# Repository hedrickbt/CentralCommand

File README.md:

# CentralCommand
Contextual Electronics CentralCommand project

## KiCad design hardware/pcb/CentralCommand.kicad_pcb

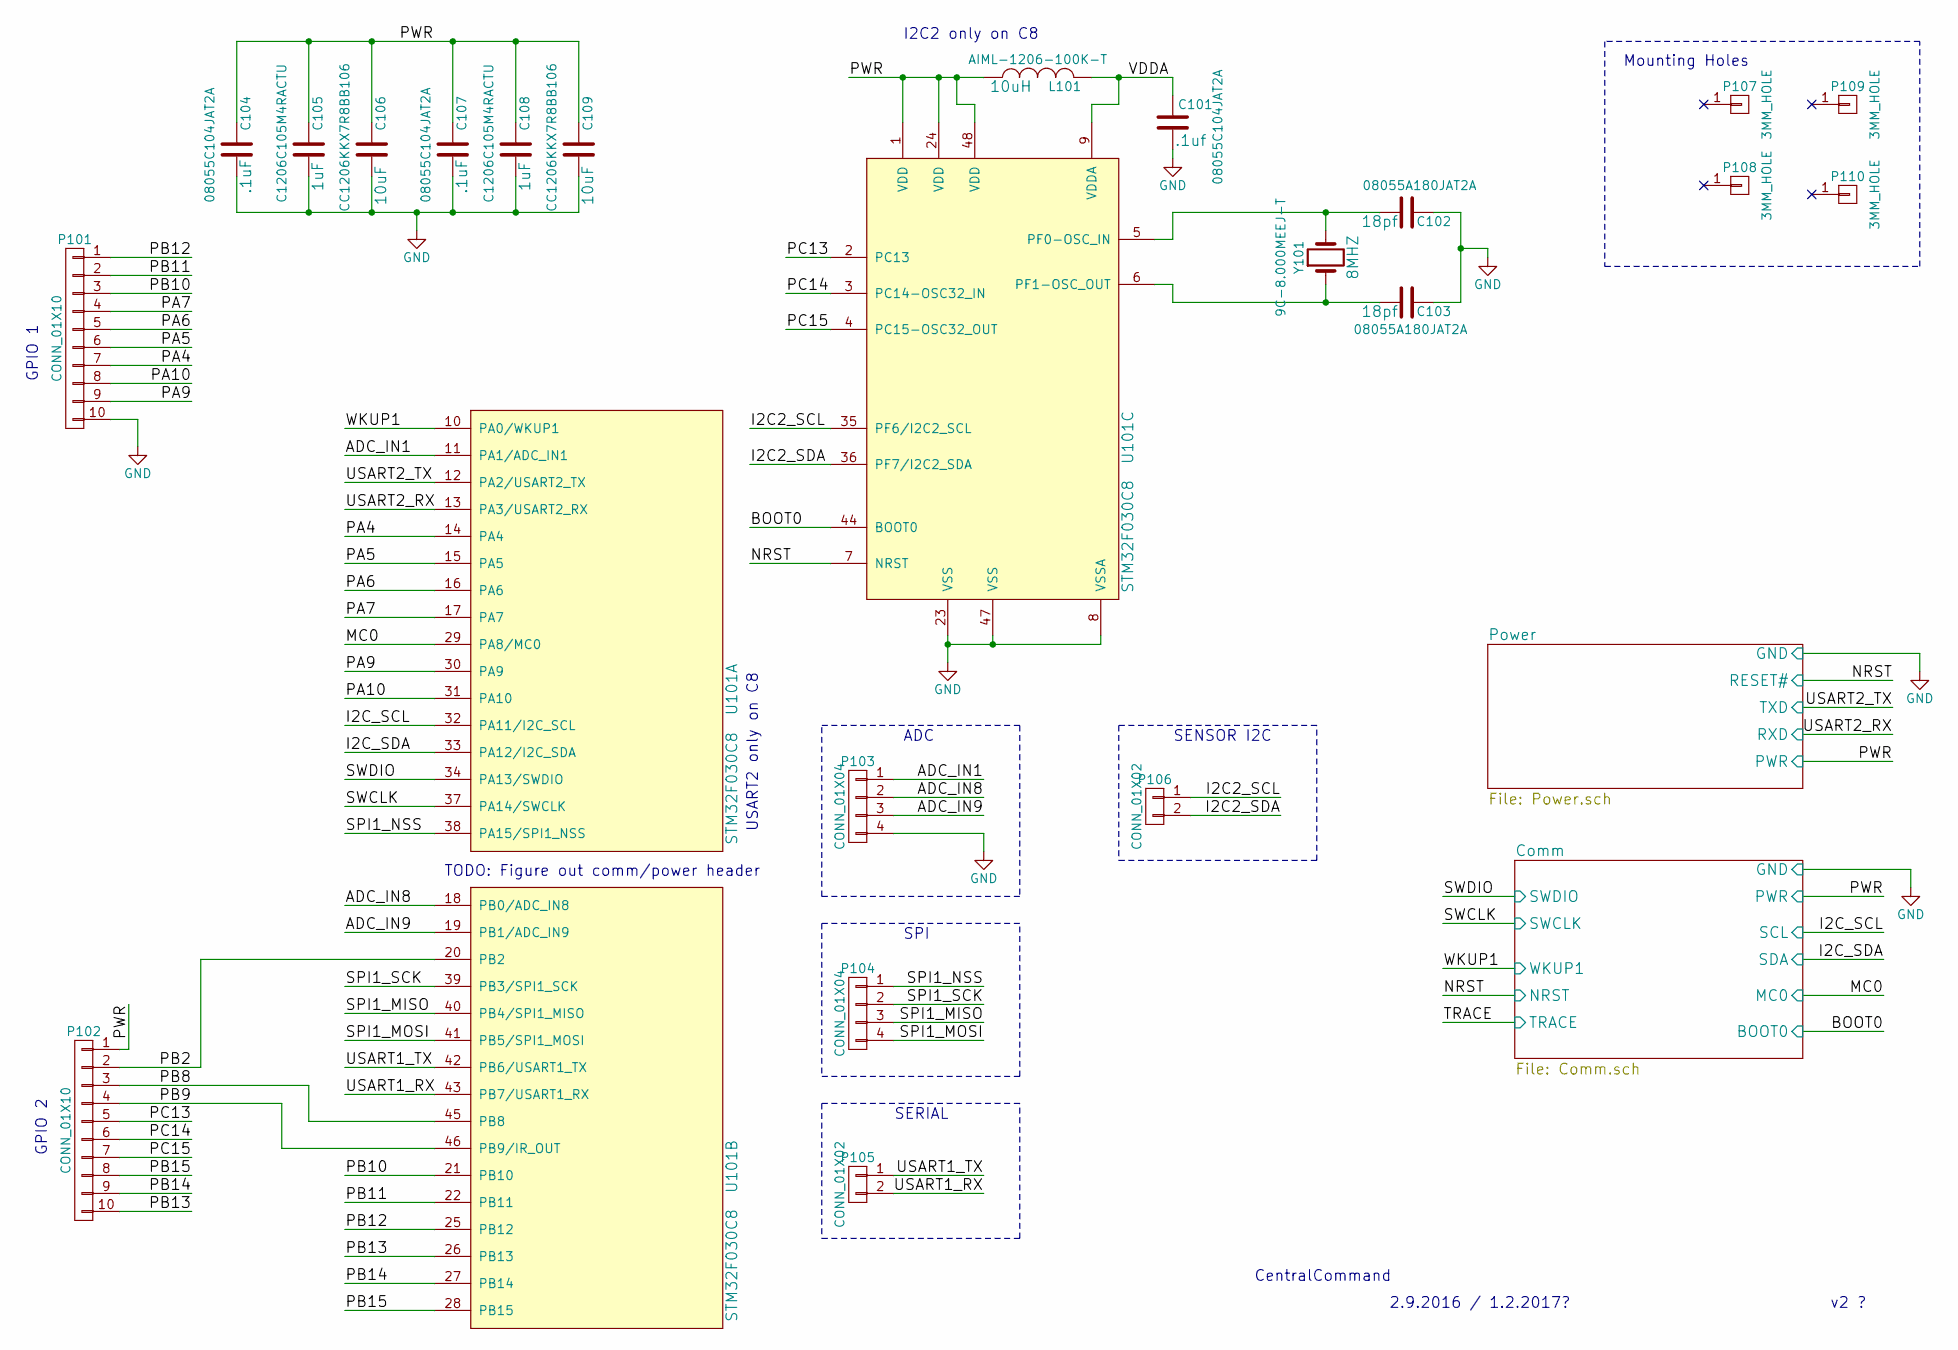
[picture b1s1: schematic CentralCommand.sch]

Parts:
C101, C104, C107: 08055C104JAT2A; C_0805; MPN 08055C104JAT2A
C102, C103: 08055A180JAT2A; C_0805; MPN 08055A180JAT2A
C105, C108: C1206C105M4RACTU; C_1206; MPN C1206C105M4RACTU
C106, C109: CC1206KKX7R8BB106; C_1206; MPN CC1206KKX7R8BB106
L101: AIML-1206-100K-T; Neosid_Inductor_SM1206; MPN AIML-1206-100K-T
P101, P102: CONN_01X10; Pin_Header_Straight_1x10
P103, P104: CONN_01X04; Pin_Header_Straight_1x04
P105, P106: CONN_01X02; Pin_Header_Straight_1x02
P107, P108, P109, P110: 3MM_HOLE; MountingHole_3mm
U101: STM32F030C8; LQFP-48_7x7mm_Pitch0.5mm; MPN STM32F030C8T6
Y101: 9C-8.000MEEJ-T; Crystal_HC49_US; MPN 9C-8.000MEEJ-T

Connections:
/ADC_IN1: P103.1, U101.11 (PA1/ADC_IN1)
/ADC_IN8: P103.2, U101.18 (PB0/ADC_IN8)
/ADC_IN9: P103.3, U101.19 (PB1/ADC_IN9)
/BOOT0: U101.44 (BOOT0); also elsewhere on the board
/I2C2_SCL: P106.1, U101.35 (PF6/I2C2_SCL)
/I2C2_SDA: P106.2, U101.36 (PF7/I2C2_SDA)
/I2C_SCL: U101.32 (PA11/I2C_SCL); also elsewhere on the board
/I2C_SDA: U101.33 (PA12/I2C_SDA); also elsewhere on the board
/MC0: U101.29 (PA8/MC0); also elsewhere on the board
/NRST: U101.7 (NRST); also elsewhere on the board
/PA4: P101.7, U101.14 (PA4)
/PA5: P101.6, U101.15 (PA5)
/PA6: P101.5, U101.16 (PA6)
/PA7: P101.4, U101.17 (PA7)
/PA9: P101.9, U101.30 (PA9)
/PA10: P101.8, U101.31 (PA10)
/PB2: P102.2, U101.20 (PB2)
/PB8: P102.3, U101.45 (PB8)
/PB9: P102.4, U101.46 (PB9/IR_OUT)
/PB10: P101.3, U101.21 (PB10)
/PB11: P101.2, U101.22 (PB11)
/PB12: P101.1, U101.25 (PB12)
/PB13: P102.10, U101.26 (PB13)
/PB14: P102.9, U101.27 (PB14)
/PB15: P102.8, U101.28 (PB15)
/PC13: P102.5, U101.2 (PC13)
/PC14: P102.6, U101.3 (PC14-OSC32_IN)
/PC15: P102.7, U101.4 (PC15-OSC32_OUT)
/PWR: C104.1, C105.1, C106.1, C107.1, C108.1, C109.1, L101.1, P102.1, U101.1 (VDD), U101.24 (VDD), U101.48 (VDD); also elsewhere on the board
/SPI1_MISO: P104.3, U101.40 (PB4/SPI1_MISO)
/SPI1_MOSI: P104.4, U101.41 (PB5/SPI1_MOSI)
/SPI1_NSS: P104.1, U101.38 (PA15/SPI1_NSS)
/SPI1_SCK: P104.2, U101.39 (PB3/SPI1_SCK)
/SWCLK: U101.37 (PA14/SWCLK); also elsewhere on the board
/SWDIO: U101.34 (PA13/SWDIO); also elsewhere on the board
/USART1_RX: P105.2, U101.43 (PB7/USART1_RX)
/USART1_TX: P105.1, U101.42 (PB6/USART1_TX)
/USART2_RX: U101.13 (PA3/USART2_RX); also elsewhere on the board
/USART2_TX: U101.12 (PA2/USART2_TX); also elsewhere on the board
/VDDA: C101.1, L101.2, U101.9 (VDDA)
/WKUP1: U101.10 (PA0/WKUP1); also elsewhere on the board
GND: C101.2, C102.1, C103.1, C104.2, C105.2, C106.2, C107.2, C108.2, C109.2, P101.10, P103.4, U101.8 (VSSA), U101.23 (VSS), U101.47 (VSS); also elsewhere on the board
unnamed: C102.2, U101.5 (PF0-OSC_IN), Y101.2
unnamed: C103.2, U101.6 (PF1-OSC_OUT), Y101.1

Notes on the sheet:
CentralCommand
v2 ?
2.9.2016 / 1.2.2017?
USART2 only on C8
I2C2 only on C8
TODO: Figure out comm/power header
GPIO 1
GPIO 2
SPI
ADC
SENSOR I2C
SERIAL
Mounting Holes

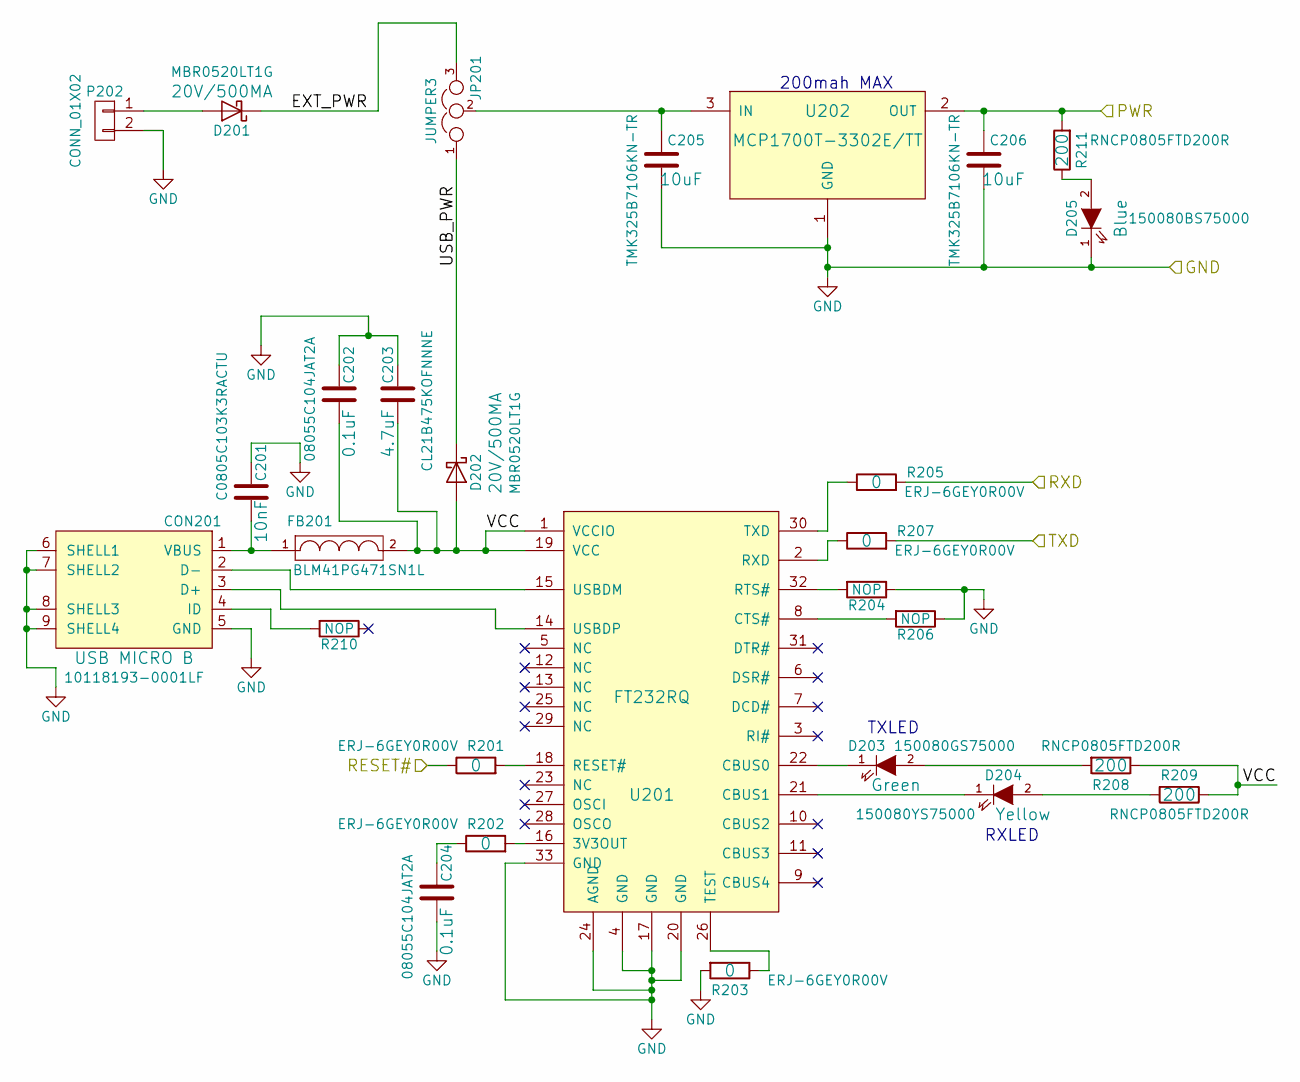
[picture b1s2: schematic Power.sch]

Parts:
C201: C0805C103K3RACTU; C_0805; MPN C0805C103K3RACTU
C202, C204: 08055C104JAT2A; C_0805; MPN 08055C104JAT2A
C203: CL21B475KOFNNNE; C_0805; MPN CL21B475KOFNNNE
C205, C206: TMK325B7106KN-TR; C_1210; MPN TMK325B7106KN-TR
CON201: 10118193-0001LF; MICRO_B_CONN_10118193-0001LF; MPN 10118193-0001LF
D201, D202: MBR0520LT1G; SOD-123; MPN MBR0520LT1G
D203: 150080GS75000; LED_0805; MPN 150080GS75000
D204: 150080YS75000; LED_0805; MPN 150080YS75000
D205: 150080BS75000; LED_0805; MPN 150080BS75000
FB201: BLM41PG471SN1L; Filter_SM1806; MPN BLM41PG471SN1L
JP201: JUMPER3; Pin_Header_Straight_1x03
P202: CONN_01X02; Pin_Header_Straight_1x02
R201, R202, R203, R205, R207: ERJ-6GEY0R00V; R_0805; MPN ERJ-6GEY0R00V
R204, R206, R210: NOP; R_0805
R208, R209, R211: RNCP0805FTD200R; R_0805; MPN RNCP0805FTD200R
U201: FT232RQ; QFN-32-1EP_5x5mm_Pitch0.5mm; MPN FT232RQ-REEL
U202: MCP1700T-3302E/TT; SOT-23; MPN MCP1700T-3302E/TT

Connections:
/NRST: R201.1; also elsewhere on the board
/PWR: C206.1, R211.2, U202.2 (OUT); also elsewhere on the board
/Power/EXT_PWR: D201.1 (K), JP201.3
/Power/USB_PWR: D202.1 (K), JP201.1
/Power/VCC: C202.2, C203.2, D202.2 (A), FB201.2, R208.1, R209.1, U201.1 (VCCIO), U201.19 (VCC)
/USART2_RX: R205.2; also elsewhere on the board
/USART2_TX: R207.2; also elsewhere on the board
GND: C201.1, C202.1, C203.1, C204.2, C205.2, C206.2, CON201.5 (GND), CON201.6 (SHELL1), CON201.7 (SHELL2), CON201.8 (SHELL3), CON201.9 (SHELL4), D205.1 (K), P202.2, R203.2, R204.1, R206.1, U201.4 (GND), U201.17 (GND), U201.20 (GND), U201.24 (AGND), U201.33 (GND), U202.1 (GND); also elsewhere on the board
unnamed: C201.2, CON201.1 (VBUS), FB201.1
unnamed: C204.1, R202.1
unnamed: C205.1, JP201.2, U202.3 (IN)
unnamed: CON201.2 (D-), U201.15 (USBDM)
unnamed: CON201.3 (D+), U201.14 (USBDP)
unnamed: CON201.4 (ID), R210.2
unnamed: D201.2 (A), P202.1
unnamed: D203.1 (K), U201.22 (CBUS0)
unnamed: D203.2 (A), R208.2
unnamed: D204.1 (K), U201.21 (CBUS1)
unnamed: D204.2 (A), R209.2
unnamed: D205.2 (A), R211.1
unnamed: R201.2, U201.18 (RESET#)
unnamed: R202.2, U201.16 (3V3OUT)
unnamed: R203.1, U201.26 (TEST)
unnamed: R204.2, U201.32 (RTS#)
unnamed: R205.1, U201.30 (TXD)
unnamed: R206.2, U201.8 (CTS#)
unnamed: R207.1, U201.2 (RXD)

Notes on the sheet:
200mah MAX
TXLED
RXLED

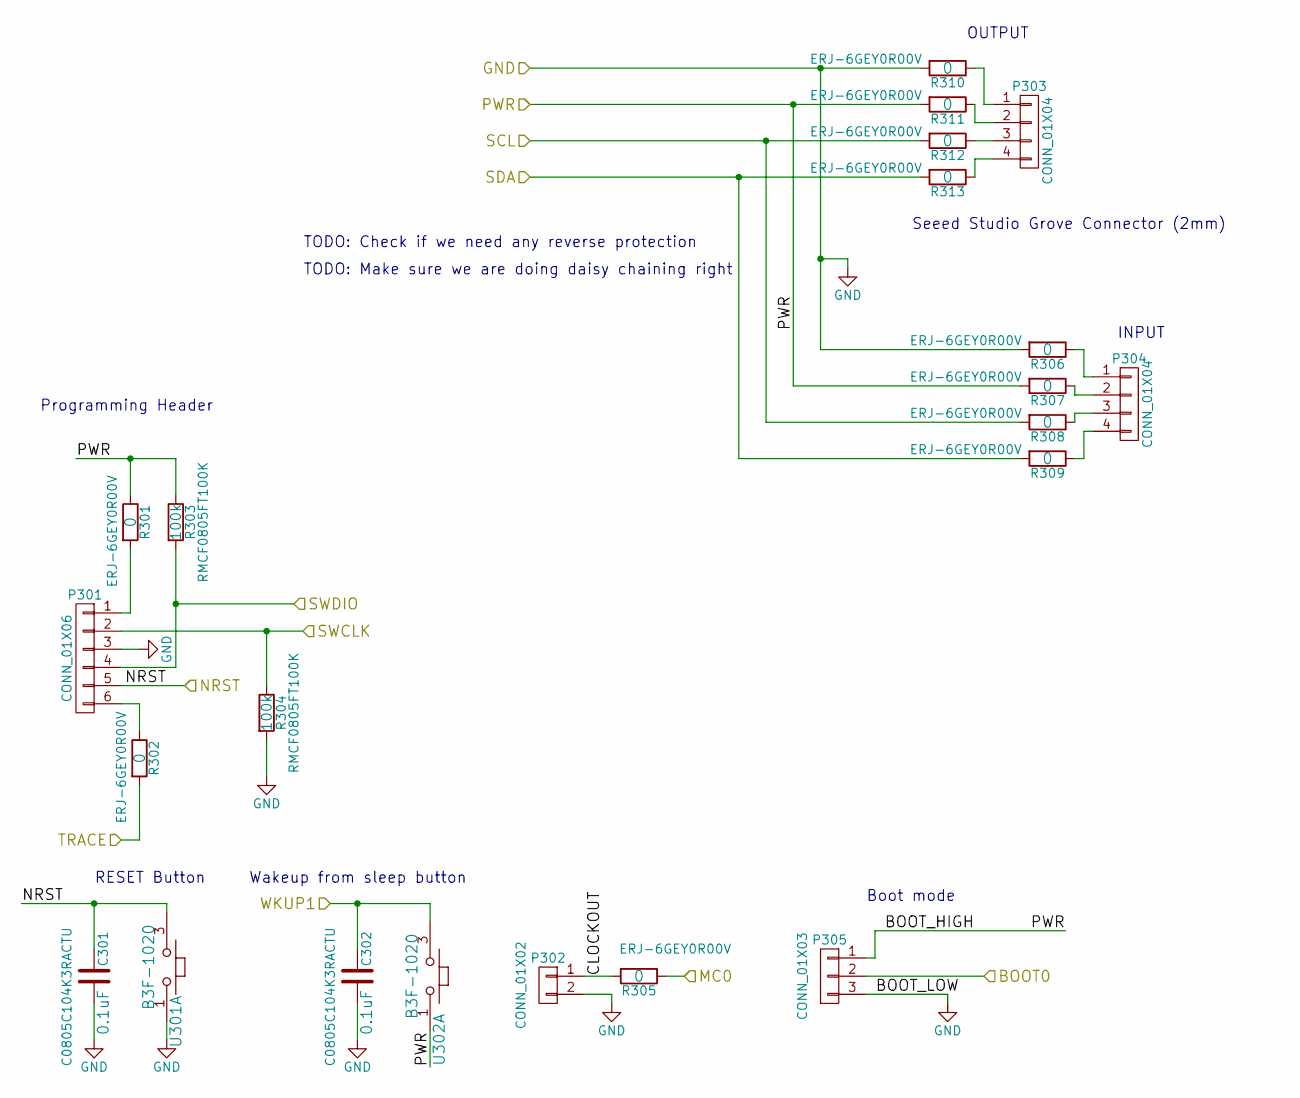
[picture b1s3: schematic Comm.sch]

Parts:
C301, C302: C0805C104K3RACTU; C_0805; MPN C0805C104K3RACTU
P301: CONN_01X06; Pin_Header_Straight_1x06
P302: CONN_01X02; Pin_Header_Straight_1x02
P303, P304: CONN_01X04; GroveConnectorStraight_B4B-PH-K-S; MPN S4B-PH-K-S(LF)(SN)
P305: CONN_01X03; Pin_Header_Straight_1x03
R301, R302, R305, R306, R307, R308, R309, R310, R311, R312, R313: ERJ-6GEY0R00V; R_0805; MPN ERJ-6GEY0R00V
R303, R304: RMCF0805FT100K; C_0805; MPN RMCF0805FT100K
U301, U302: B3F-1020; Pushbutton_B3F-1020; MPN B3F-1020

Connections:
/BOOT0: P305.2; also elsewhere on the board
/Comm/CLOCKOUT: P302.1, R305.2
/I2C_SCL: R308.2, R312.2; also elsewhere on the board
/I2C_SDA: R309.2, R313.2; also elsewhere on the board
/MC0: R305.1; also elsewhere on the board
/NRST: C301.1, P301.5, U301.3; also elsewhere on the board
/PWR: P305.1, R301.1, R303.1, R307.2, R311.2, U302.1; also elsewhere on the board
/SWCLK: P301.2, R304.1; also elsewhere on the board
/SWDIO: P301.4, R303.2; also elsewhere on the board
/TRACE: R302.2
/WKUP1: C302.1, U302.3; also elsewhere on the board
GND: C301.2, C302.2, P301.3, P302.2, P305.3, R304.2, R306.2, R310.2, U301.1; also elsewhere on the board
unnamed: P301.1, R301.2
unnamed: P301.6, R302.1
unnamed: P303.1, R310.1
unnamed: P303.2, R311.1
unnamed: P303.3, R312.1
unnamed: P303.4, R313.1
unnamed: P304.1, R306.1
unnamed: P304.2, R307.1
unnamed: P304.3, R308.1
unnamed: P304.4, R309.1

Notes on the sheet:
Seeed Studio Grove Connector (2mm)
TODO: Check if we need any reverse protection
TODO: Make sure we are doing daisy chaining right
RESET Button
Programming Header
Wakeup from sleep button
Boot mode
OUTPUT
INPUT

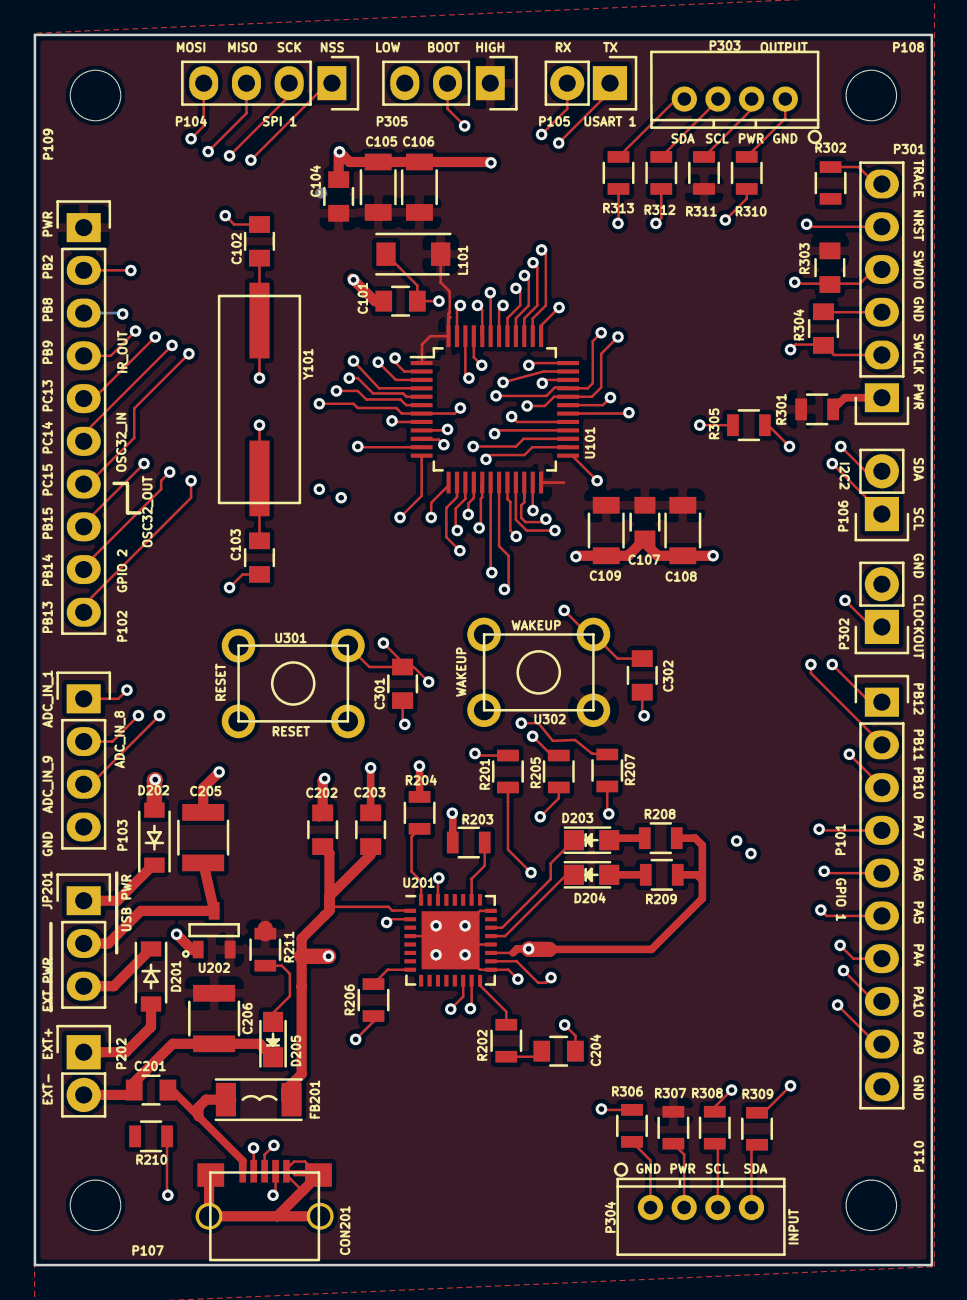
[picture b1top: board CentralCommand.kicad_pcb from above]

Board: 4 copper layers, 53.3 x 73.1 mm, 72 parts (0 on the bottom side), 77 nets.

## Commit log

2016-12-29 Moving items around
2016-12-29 Opened and saved with KiCad 4.0.5
2016-12-29 moved .gitignore from root to hardware
2016-12-31 CC51
2016-12-31 CC53
2017-01-02 CC54
2017-01-02 CC56
2017-01-02 Re-reading the netlist in pcbnew broke the Front CU as KiCad has changed the sheet mapping of nets. /comm/pwr became just /pwr. I had to associate /pwr to the Front CU.
2017-01-02 CC57
2017-01-05 CC58
